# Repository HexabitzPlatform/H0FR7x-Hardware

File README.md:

# H0FR7x-Hardware
Hexabitz SPST 18V/20A MOSFET Switch Module Hardware Design

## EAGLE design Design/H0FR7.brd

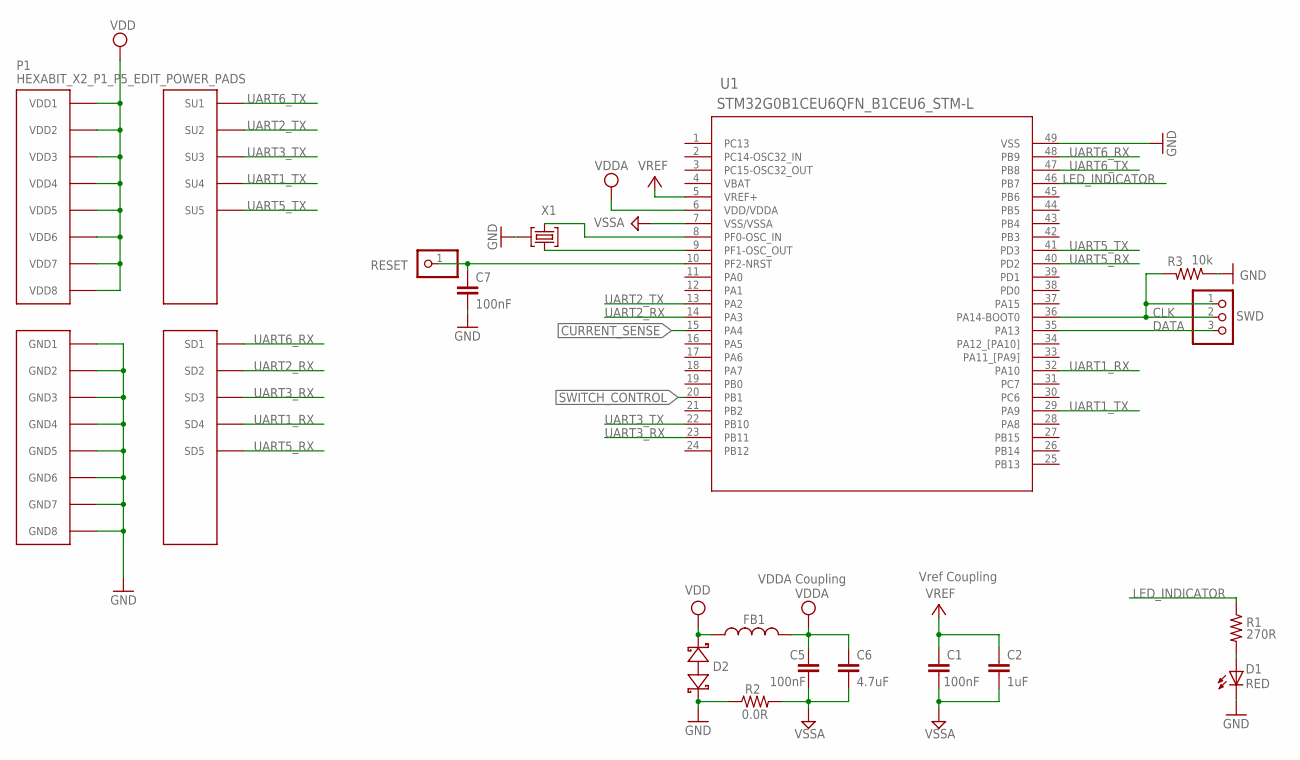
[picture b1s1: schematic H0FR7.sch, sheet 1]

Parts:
C1, C7: 100nF; C-0603; TOLERANCE 10%; VOLTAGE_RATING 10V; MPN C0603C104K8RACTU
C2: 1uF; C-0805
C5: 100nF; C-0603
C6: 4.7uF; C-0805
D1: RED; VLMS1300-GS08; MPN VLMS1300-GS08
D2: BOURNS_CDSOD323-T03SCBOURNS_CDSOD323-T03SC_0_0; BOURNS_CDSOD323-T03SC_0
FB1: FB-0603
P1: HEXABIT_X2_P1_P5_EDIT_POWER_PADS
R1: 270R; R-0603
R2: 0.0R; R-0603
R3: 10k; R-0603; TOLERANCE 5%; MPN RC0603JR-0710KL
RESET: R; 1X01
SWD: PINHD-1X3SWD; SWD
TRIMBLE-LOGO2: HEXA-LOGO
U1: STM32G0B1CEU6QFN_B1CEU6_STM-L; QFN_B1CEU6_STM-L
X1: XTALL_CSTCE8M00G52

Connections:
CLK: R3.2, SWD.1, SWD.2, U1.36 (PA14-BOOT0)
CURRENT_SENSE: U1.15 (PA4); also elsewhere on the board
DATA: SWD.3, U1.35 (PA13)
GND: C7.2, D1.C, D2.2 (C), P1.PAD_PD11 (GND1), P1.PAD_PD12 (GND2), P1.PAD_PD13 (GND3), P1.PAD_PD14 (GND4), P1.PAD_PD17 (GND5), P1.PAD_PD18 (GND6), P1.PAD_PD19 (GND7), P1.PAD_PD20 (GND8), R2.1, R3.1, U1.49 (VSS), X1.P$2 (2)
LED_INDICATOR: R1.1, U1.46 (PB7)
unnamed: U1.9 (PF1-OSC_OUT), X1.P$3 (3)
unnamed: U1.8 (PF0-OSC_IN), X1.P$1 (1)
unnamed: D1.A, R1.2
unnamed: C7.1, RESET.1, U1.10 (PF2-NRST)
SWITCH_CONTROL: U1.20 (PB1); also elsewhere on the board
UART1_RX: P1.PAD_PD4 (SD4), U1.32 (PA10)
UART1_TX: P1.PAD_PU4 (SU4), U1.29 (PA9)
UART2_RX: P1.PAD_PD2 (SD2), U1.14 (PA3)
UART2_TX: P1.PAD_PU2 (SU2), U1.13 (PA2)
UART3_RX: P1.PAD_PD3 (SD3), U1.23 (PB11)
UART3_TX: P1.PAD_PU3 (SU3), U1.22 (PB10)
UART5_RX: P1.PAD_PD5 (SD5), U1.40 (PD2)
UART5_TX: P1.PAD_PU5 (SU5), U1.41 (PD3)
UART6_RX: P1.PAD_PD1 (SD1), U1.48 (PB9)
UART6_TX: P1.PAD_PU1 (SU1), U1.47 (PB8)
VDD: D2.1 (A), FB1.1, P1.PAD_PU11 (VDD1), P1.PAD_PU12 (VDD2), P1.PAD_PU13 (VDD3), P1.PAD_PU14 (VDD4), P1.PAD_PU17 (VDD5), P1.PAD_PU18 (VDD6), P1.PAD_PU19 (VDD7), P1.PAD_PU20 (VDD8)
VDDA: C5.1, C6.1, FB1.2, U1.6 (VDD/VDDA); also elsewhere on the board
VREF: C1.1, C2.1, U1.5 (VREF+)
VSSA: C1.2, C2.2, C5.2, C6.2, R2.2, U1.7 (VSS/VSSA); also elsewhere on the board

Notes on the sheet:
Vref Coupling
VDDA Coupling

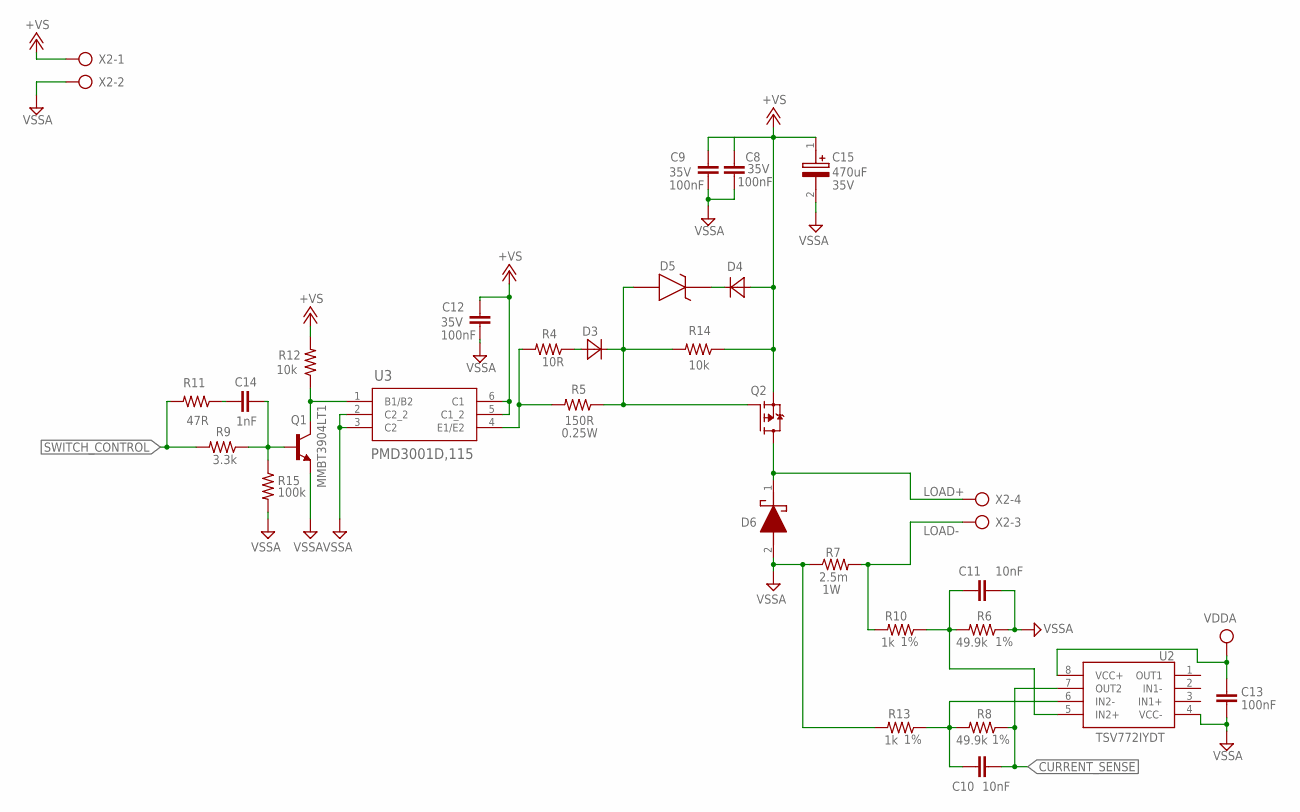
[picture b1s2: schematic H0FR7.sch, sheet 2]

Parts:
C8, C9, C12: C-0603; VOLTAGE_RATING 35V
C10, C11: 10nF; C-0603; TOLERANCE 10V; VOLTAGE_RATING 10%; MPN C0603C104K8RACTU
C13: 100nF; C-0603; TOLERANCE 10V; VOLTAGE_RATING 10%; MPN C0603C104K8RACTU
C14: 1nF; C-0603; TOLERANCE 10%; VOLTAGE_RATING 10V; MPN C0603C104K8RACTU
C15: ESH477M035AH3AA; CAPPRD500W60D1000H1700
D3, D4: DIOD-SOD-123; SOD123; MPN 1N4148W-7-F
D5: MMSZ4705T1GMMSZ4705T1G; DIO_MMSZ4700T1G; VOLTAGE 18V; MPN MMSZ4678T1G
D6: V8PAM10S-M3_H; V8PAM10SHM3H
Q1: MMBT3904LT1
Q2: STD36P4LLF6; DPAK-3
R4: 10R; R-0603; TOLERANCE 5%; MPN RC0603JR-07680KL
R5: 150R; R-0603; MPN CRGP0603F150R
R6, R8: 49.9k; R-0603; TOLERANCE 1%; MPN RC0603JR-071KL
R7: 2.5m; R1206; MPN PA1206FRE472U5Z
R9: 3.3k; R-0603; TOLERANCE 5%; MPN RC0603JR-07680KL
R10, R13: 1k; R-0603; TOLERANCE 1%; MPN RC0603JR-071KL
R11: 47R; R-0603; TOLERANCE 5%; MPN RC0603JR-07680KL
R12: 10k; R-0603; TOLERANCE 5%; MPN RC0603JR-0710KL
R14: 10k; R-0603; TOLERANCE 5%; MPN RC0603JR-07680KL
R15: 100k; R-0603; TOLERANCE 5%; MPN RC0603JR-07680KL
U2: TSV772IYDT; SOIC127P600X175-8N
U3: PMD3001D,115; SOT457_NEX
X2: AK300/4

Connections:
+VS: C8.2, C9.2, C12.2, C15.1 (+), D4.1 (A), Q2.3 (S), R12.2, R14.1, U3.5 (C1_2), U3.6 (C1), X2.1
CURRENT_SENSE: C10.2, R8.1, U2.7 (OUT2); also elsewhere on the board
LOAD+: D6.1 (K), Q2.4 (D), X2.4
LOAD-: R7.2, R10.2, X2.3
unnamed: Q1.3 (C), R12.1, U3.1 (B1/B2)
unnamed: C11.1, R6.2, R10.1, U2.5 (IN2+)
unnamed: D4.2 (C), D5.K
unnamed: C10.1, R8.2, R13.1, U2.6 (IN2-)
unnamed: D3.1 (A), R4.1
unnamed: C14.2, Q1.1 (B), R9.1, R15.1
unnamed: C14.1, R11.1
unnamed: R4.2, R5.2, U3.4 (E1/E2)
unnamed: D3.2 (C), D5.A, Q2.1 (G), R5.1, R14.2
SWITCH_CONTROL: R9.2, R11.2; also elsewhere on the board
VDDA: C13.2, U2.8 (VCC+); also elsewhere on the board
VSSA: C8.1, C9.1, C11.2, C12.1, C13.1, C15.2 (-), D6.2 (A), Q1.2 (E), R6.1, R7.1, R13.2, R15.2, U2.4 (VCC-), U3.2 (C2_2), U3.3 (C2), X2.2; also elsewhere on the board

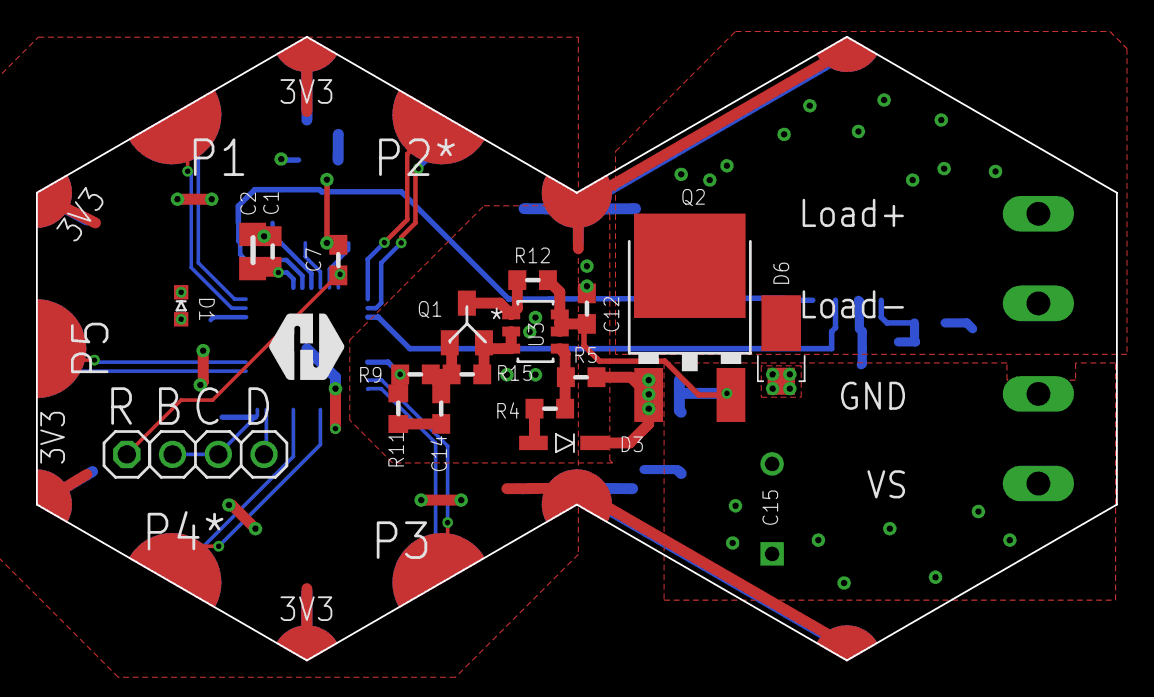
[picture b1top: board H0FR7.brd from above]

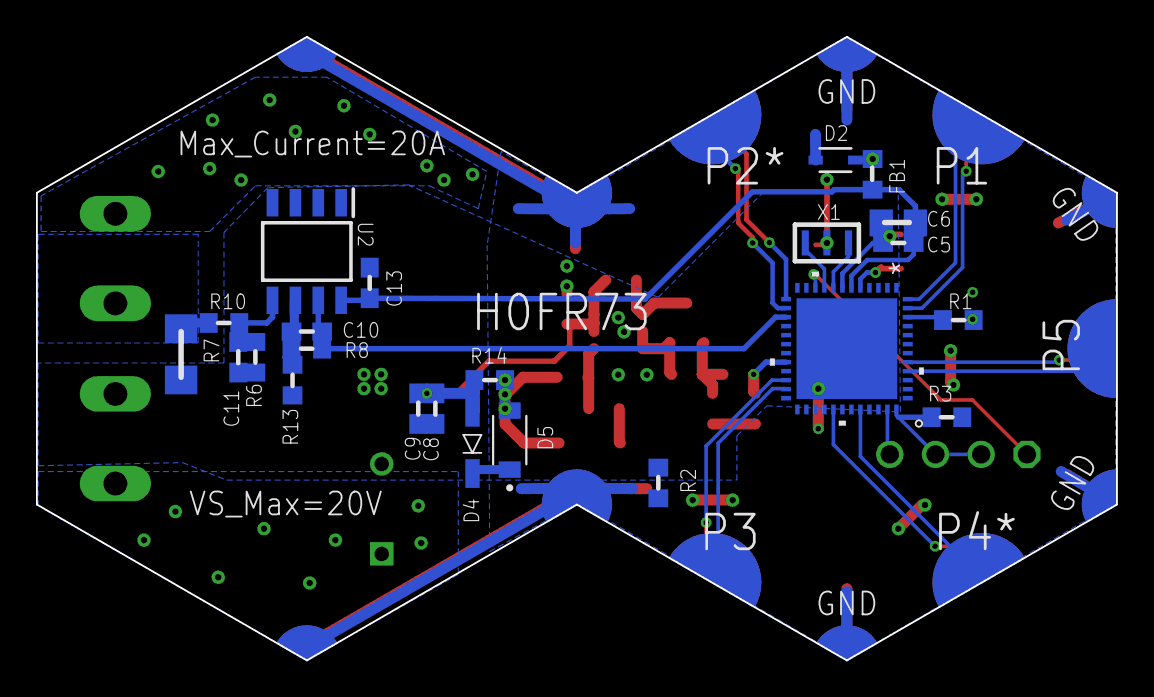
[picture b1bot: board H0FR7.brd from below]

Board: 2 copper layers, 60.0 x 34.6 mm, 46 parts (23 on the bottom side), 36 nets.

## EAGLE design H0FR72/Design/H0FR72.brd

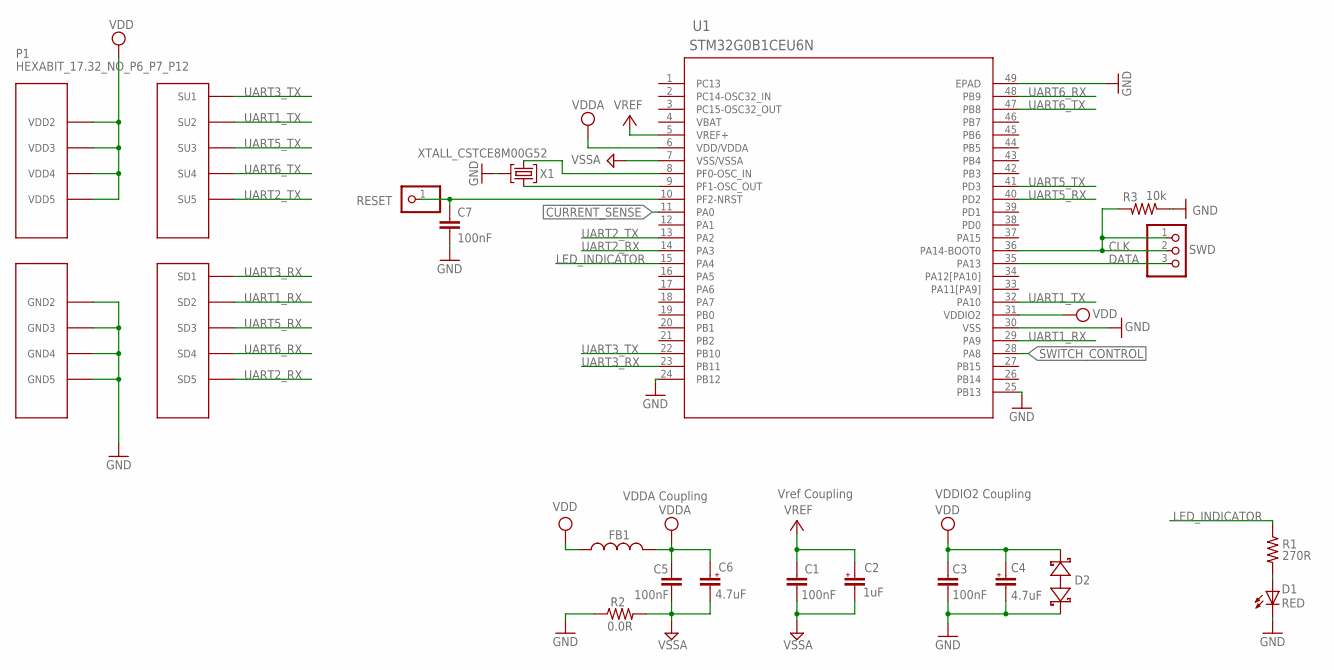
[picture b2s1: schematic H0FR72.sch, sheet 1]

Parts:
C1, C3, C7: 100nF; C-0402; TOLERANCE 10%; VOLTAGE_RATING 10V; MPN C0603C104K8RACTU
C2: 1uF; C-0603-POL; TOLERANCE 10%; VOLTAGE_RATING 16V; MPN CC0805KKX7R7BB105
C4, C6: 4.7uF; C-0603-POL; TOLERANCE 10%; VOLTAGE_RATING 25V; MPN GRM21BC81E475KA12L
C5: 100nF; C-0603
D1: RED; VLMS1300-GS08; MPN VLMS1300-GS08
D2: BOURNS_CDSOD323-T03SCBOURNS_CDSOD323-T03SC_0_0; BOURNS_CDSOD323-T03SC_0
FB1: FB-0603
P1: HEXABIT_17.32_NO_P6_P7_P12
R1: 270R; R-0603
R2: 0.0R; R-0603
R3: 10k; R-0402; TOLERANCE 5%; MPN RC0603JR-0710KL
RESET: R; 1X01
SWD: PINHD-1X3SWD; SWD
TRIMBLE-LOGO2: HEXA-LOGO
U1: STM32G0B1CEU6N; HEXABITZ_ICS_QFN_B1CEU6_STM-L
X1: XTALL_CSTCE8M00G52

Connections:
CLK: R3.2, SWD.1, SWD.2, U1.36 (PA14-BOOT0)
CURRENT_SENSE: U1.11 (PA0); also elsewhere on the board
DATA: SWD.3, U1.35 (PA13)
GND: C3.2, C4.2, C7.2, D1.C, D2.2 (C), P1.PAD_PD8 (GND2), P1.PAD_PD9 (GND3), P1.PAD_PD10 (GND4), P1.PAD_PD11 (GND5), R2.1, R3.1, U1.24 (PB12), U1.25 (PB13), U1.30 (VSS), U1.49 (EPAD), X1.P$2 (2)
LED_INDICATOR: R1.1, U1.15 (PA4)
unnamed: U1.9 (PF1-OSC_OUT), X1.P$3 (3)
unnamed: U1.8 (PF0-OSC_IN), X1.P$1 (1)
unnamed: D1.A, R1.2
unnamed: C7.1, RESET.1, U1.10 (PF2-NRST)
SWITCH_CONTROL: U1.28 (PA8); also elsewhere on the board
UART1_RX: P1.PAD_PD2 (SD2), U1.29 (PA9)
UART1_TX: P1.PAD_PU2 (SU2), U1.32 (PA10)
UART2_RX: P1.PAD_PD5 (SD5), U1.14 (PA3)
UART2_TX: P1.PAD_PU5 (SU5), U1.13 (PA2)
UART3_RX: P1.PAD_PD1 (SD1), U1.23 (PB11)
UART3_TX: P1.PAD_PU1 (SU1), U1.22 (PB10)
UART5_RX: P1.PAD_PD3 (SD3), U1.40 (PD2)
UART5_TX: P1.PAD_PU3 (SU3), U1.41 (PD3)
UART6_RX: P1.PAD_PD4 (SD4), U1.48 (PB9)
UART6_TX: P1.PAD_PU4 (SU4), U1.47 (PB8)
VBAT: U1.4 (VBAT)
VDD: C3.1, C4.1, D2.1 (A), FB1.1, P1.PAD_PU8 (VDD2), P1.PAD_PU9 (VDD3), P1.PAD_PU10 (VDD4), P1.PAD_PU11 (VDD5), U1.31 (VDDIO2)
VDDA: C5.1, C6.1, FB1.2, U1.6 (VDD/VDDA)
VREF: C1.1, C2.1, U1.5 (VREF+)
VSSA: C1.2, C2.2, C5.2, C6.2, R2.2, U1.7 (VSS/VSSA); also elsewhere on the board

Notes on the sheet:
VDDIO2 Coupling
Vref Coupling
VDDA Coupling

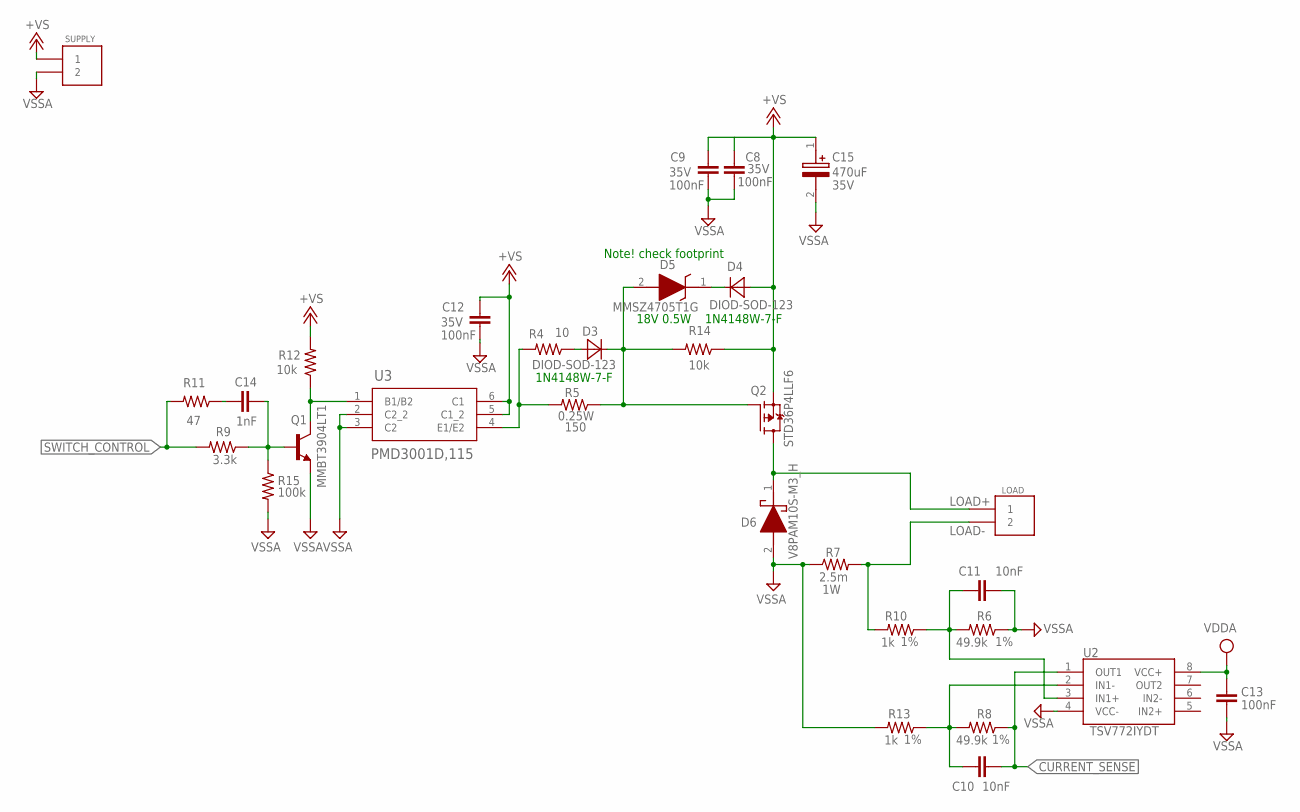
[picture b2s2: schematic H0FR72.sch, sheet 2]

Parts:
C8, C9, C12: C-0402; VOLTAGE_RATING 35V
C10, C11: 10nF; C-0402; TOLERANCE 10V; VOLTAGE_RATING 10%; MPN C0603C104K8RACTU
C13: 100nF; C-0402; TOLERANCE 10V; VOLTAGE_RATING 10%; MPN C0603C104K8RACTU
C14: 1nF; C-0402; TOLERANCE 10%; VOLTAGE_RATING 10V; MPN C0603C104K8RACTU
C15: ESH477M035AH3AA; CAPPRD500W60D1000H1700
D3, D4: DIOD-SOD-123; SOD123
D5: MMSZ4705T1G; SOD3716X135N
D6: V8PAM10S-M3_H; V8PAM10SHM3H
LOAD: 1546111-2
Q1: MMBT3904LT1
Q2: STD36P4LLF6; DPAK-3
R4: 10; R-0402; TOLERANCE 5%; MPN RC0603JR-07680KL
R5: 150; R-0402; TOLERANCE 5%; MPN RC0603JR-07680KL
R6, R8: 49.9k; R-0402; TOLERANCE 1%; MPN RC0603JR-071KL
R7: 2.5m; R2512
R9: 3.3k; R-0402; TOLERANCE 5%; MPN RC0603JR-07680KL
R10, R13: 1k; R-0402; TOLERANCE 1%; MPN RC0603JR-071KL
R11: 47; R-0402; TOLERANCE 5%; MPN RC0603JR-07680KL
R12: 10k; R-0402; TOLERANCE 5%; MPN RC0603JR-0710KL
R14: 10k; R-0402; TOLERANCE 5%; MPN RC0603JR-07680KL
R15: 100k; R-0402; TOLERANCE 5%; MPN RC0603JR-07680KL
SUPPLY: 1546111-2
TRIMBLE-LOGO1: HEXA-LOGO
U2: TSV772IYDT; SOIC127P600X175-8N
U3: PMD3001D,115; SOT457_NEX

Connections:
+VS: C8.2, C9.2, C12.2, C15.1 (+), D4.1 (A), Q2.3 (S), R12.2, R14.1, SUPPLY.1, U3.5 (C1_2), U3.6 (C1)
CURRENT_SENSE: C10.2, R8.1, U2.1 (OUT1); also elsewhere on the board
LOAD+: D6.1 (K), LOAD.1, Q2.4 (D)
LOAD-: LOAD.2, R7.2, R10.2
unnamed: Q1.3 (C), R12.1, U3.1 (B1/B2)
unnamed: C11.1, R6.2, R10.1, U2.3 (IN1+)
unnamed: D4.2 (C), D5.1 (K)
unnamed: C10.1, R8.2, R13.1, U2.2 (IN1-)
unnamed: D3.1 (A), R4.1
unnamed: C14.2, Q1.1 (B), R9.1, R15.1
unnamed: C14.1, R11.1
unnamed: R4.2, R5.2, U3.4 (E1/E2)
unnamed: D3.2 (C), D5.2 (A), Q2.1 (G), R5.1, R14.2
SWITCH_CONTROL: R9.2, R11.2; also elsewhere on the board
VCC: C13.2, U2.8 (VCC+)
VSSA: C8.1, C9.1, C11.2, C12.1, C13.1, C15.2 (-), D6.2 (A), Q1.2 (E), R6.1, R7.1, R13.2, R15.2, SUPPLY.2, U2.4 (VCC-), U3.2 (C2_2), U3.3 (C2); also elsewhere on the board

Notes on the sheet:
1N4148W-7-F
18V 0.5W
Note! check footprint

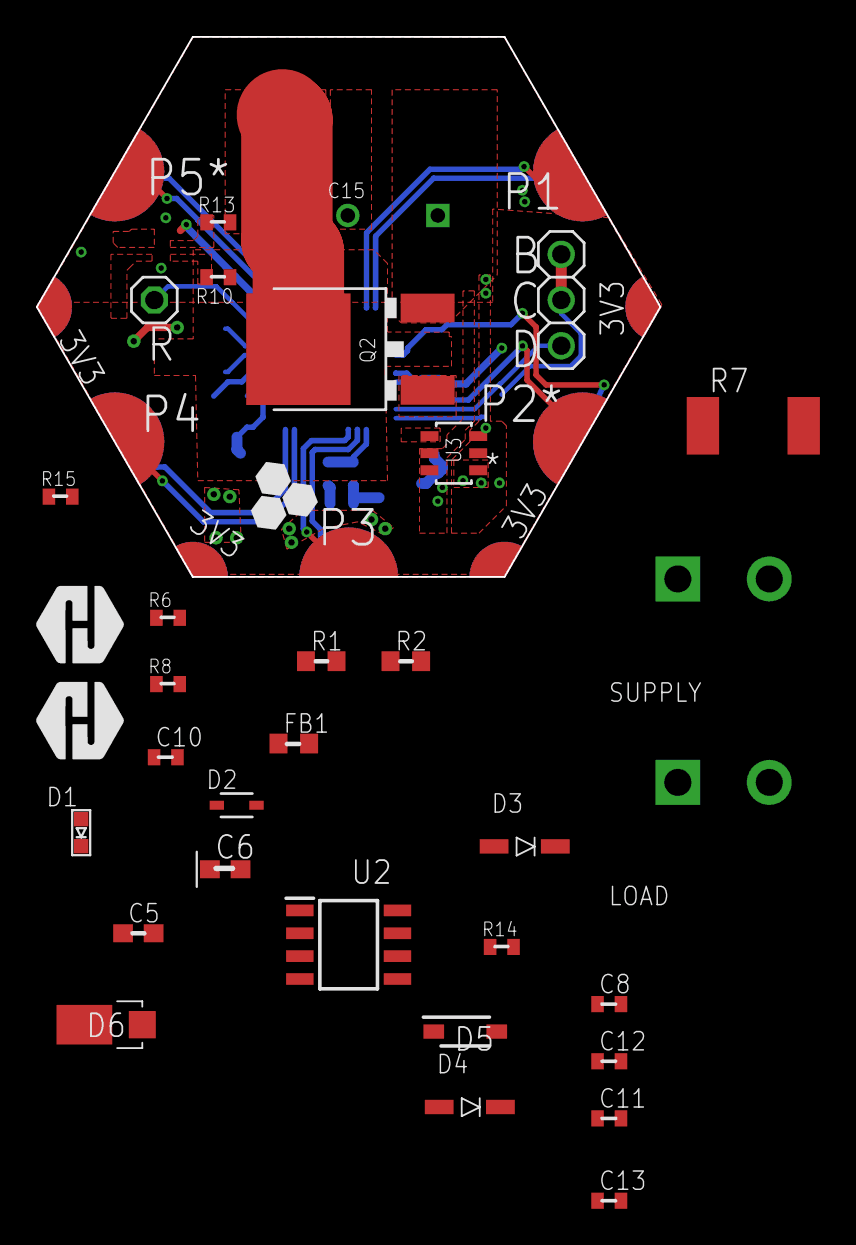
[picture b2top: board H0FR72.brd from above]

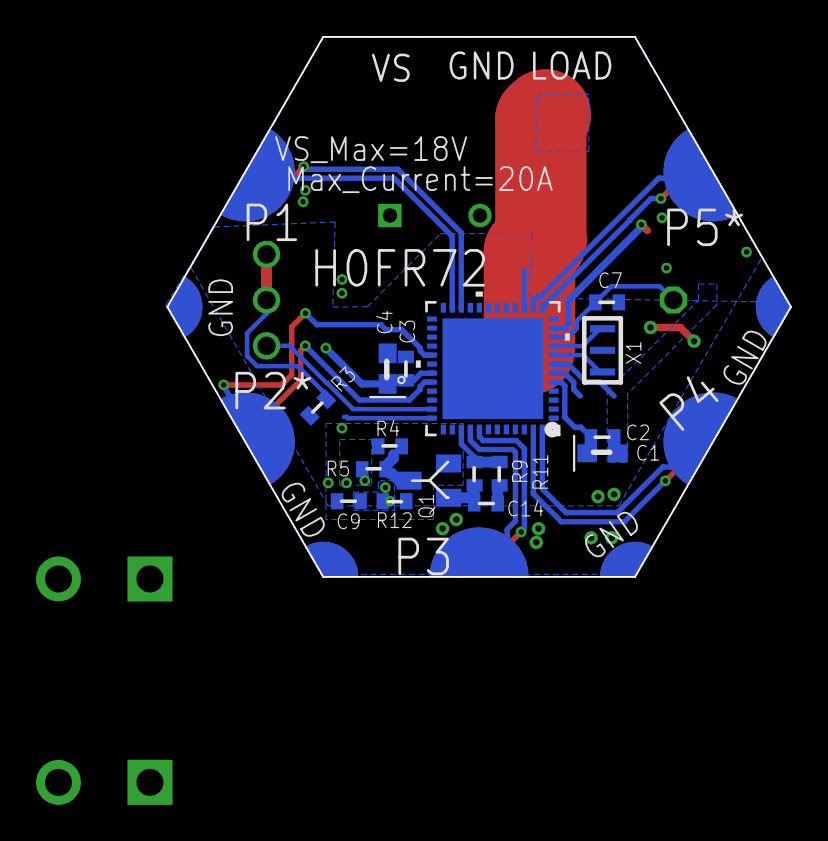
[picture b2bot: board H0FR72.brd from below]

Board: 2 copper layers, 34.6 x 30.0 mm, 50 parts (17 on the bottom side), 37 nets.

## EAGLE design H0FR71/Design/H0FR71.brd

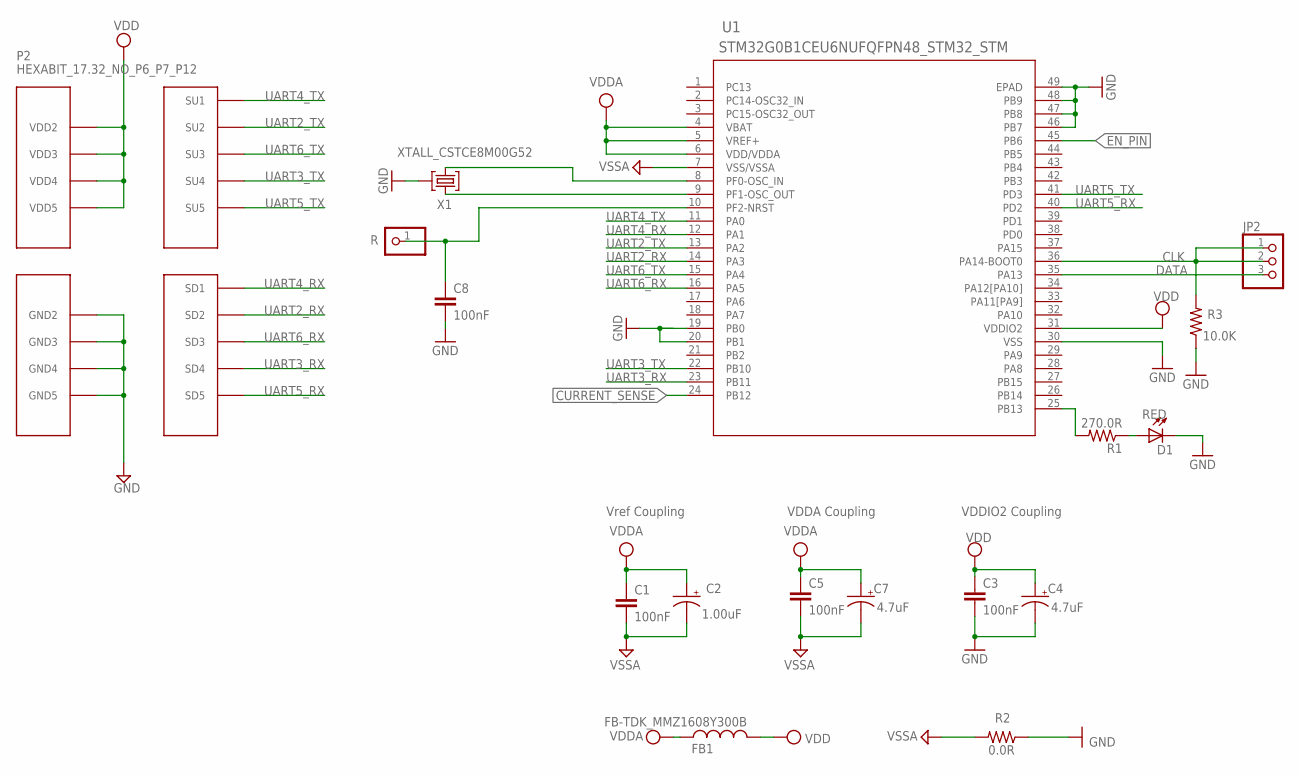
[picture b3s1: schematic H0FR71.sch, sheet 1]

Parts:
C1, C3, C8: 100nF; C-0603; TOLERANCE 10%; VOLTAGE_RATING 10V; MPN C0603C104K8RACTU
C2: 1.00uF; C-0805-POL; TOLERANCE 10%; VOLTAGE_RATING 16V; MPN CC0805KKX7R7BB105
C4, C7: 4.7uF; C-0805-POL; TOLERANCE 10%; VOLTAGE_RATING 25V; MPN GRM21BC81E475KA12L
C5: 100nF; C-0603; TOLERANCE 10%; VOLTAGE_RATING 10; MPN C0603C104K8RACTU
D1: RED; VLMS1300-GS08; MPN VLMS1300-GS08
FB1: FB-TDK_MMZ1608Y300B; MPN MMZ1608Y300B
JP2: PINHD-1X3; 1X03
P2: HEXABIT_17.32_NO_P6_P7_P12
R: PINHD-1X1; 1X01
R1: 270.0R; R-0603; TOLERANCE 1%; MPN RC0603FR-07270RL
R2: 0.0R; R-0603; MPN RC0603JR-070RL
R3: 10.0K; R-0603; TOLERANCE 5%; MPN RC0603JR-0710KL
U1: STM32G0B1CEU6NUFQFPN48_STM32_STM; UFQFPN48_STM32_STM
X1: XTALL_CSTCE8M00G52

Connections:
AGND: C1.2, C2.2 (-), C5.2, C7.2 (-), R2.2, U1.7 (VSS/VSSA); also elsewhere on the board
CLK: JP2.1, JP2.2, R3.2, U1.36 (PA14-BOOT0)
CURRENT_SENSE: U1.24 (PB12); also elsewhere on the board
DATA: JP2.3, U1.35 (PA13)
EN_PIN: U1.45 (PB6); also elsewhere on the board
GND: C3.2, C4.2 (-), C8.2, D1.C, P2.PAD_PD8 (GND2), P2.PAD_PD9 (GND3), P2.PAD_PD10 (GND4), P2.PAD_PD11 (GND5), R2.1, R3.1, U1.19 (PB0), U1.20 (PB1), U1.30 (VSS), U1.46 (PB7), U1.47 (PB8), U1.48 (PB9), U1.49 (EPAD), X1.P$2 (2); also elsewhere on the board
unnamed: U1.9 (PF1-OSC_OUT), X1.P$3 (3)
unnamed: U1.8 (PF0-OSC_IN), X1.P$1 (1)
unnamed: R1.2, U1.25 (PB13)
unnamed: D1.A, R1.1
unnamed: C8.1, R.1, U1.10 (PF2-NRST)
UART2_RX: P2.PAD_PD2 (SD2), U1.14 (PA3)
UART2_TX: P2.PAD_PU2 (SU2), U1.13 (PA2)
UART3_RX: P2.PAD_PD4 (SD4), U1.23 (PB11)
UART3_TX: P2.PAD_PU4 (SU4), U1.22 (PB10)
UART4_RX: P2.PAD_PD1 (SD1), U1.12 (PA1)
UART4_TX: P2.PAD_PU1 (SU1), U1.11 (PA0)
UART5_RX: P2.PAD_PD5 (SD5), U1.40 (PD2)
UART5_TX: P2.PAD_PU5 (SU5), U1.41 (PD3)
UART6_RX: P2.PAD_PD3 (SD3), U1.16 (PA5)
UART6_TX: P2.PAD_PU3 (SU3), U1.15 (PA4)
VDD: C3.1, C4.1 (+), FB1.2, P2.PAD_PU8 (VDD2), P2.PAD_PU9 (VDD3), P2.PAD_PU10 (VDD4), P2.PAD_PU11 (VDD5), U1.31 (VDDIO2)
VDDA: C1.1, C2.1 (+), C5.1, C7.1 (+), FB1.1, U1.4 (VBAT), U1.5 (VREF+), U1.6 (VDD/VDDA); also elsewhere on the board

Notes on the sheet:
VDDA Coupling
VDDIO2 Coupling
Vref Coupling

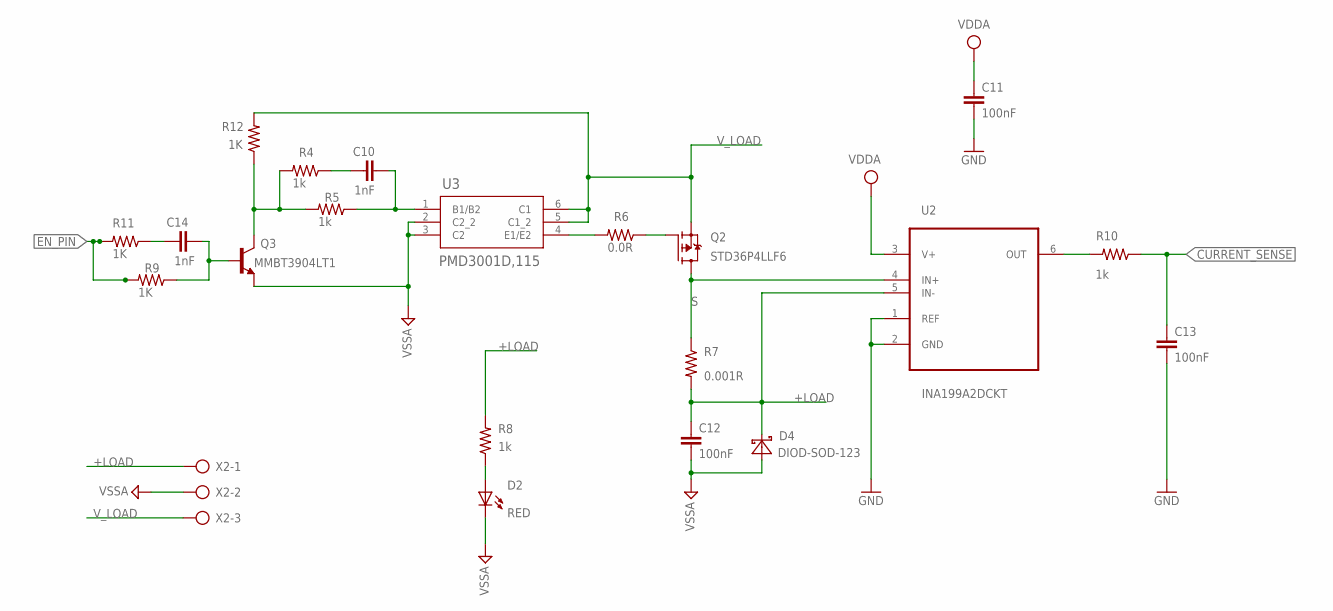
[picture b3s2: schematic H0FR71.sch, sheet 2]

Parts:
C10, C14: 1nF; C-0603; TOLERANCE 10%; VOLTAGE_RATING 10V; MPN C0603C104K8RACTU
C11: 100nF; C-0603; TOLERANCE 10V; VOLTAGE_RATING 10%; MPN C0603C104K8RACTU
C12, C13: 100nF; C-0603; TOLERANCE 10%; VOLTAGE_RATING 10V; MPN C0603C104K8RACTU
D2: RED; VLMS1300-GS08; MPN VLMO1300-GS08
D4: DIOD-SOD-123; SOD123
Q2: STD36P4LLF6; DPAK-3
Q3: MMBT3904LT1
R4, R5: 1k; R-0603; TOLERANCE 5%; MPN RC0603JR-07680KL
R6: 0.0R; R-0603; MPN RC0603JR-070RL
R7: 0.001R; R2512
R8: 1k; R-0603; TOLERANCE 1%; MPN RC0603JR-071KL
R9, R11: 1K; R-0603; TOLERANCE 5%; MPN RC0603JR-07680KL
R10: 1k; R-0603; TOLERANCE 5%; MPN RC0603JR-071KL
R12: 1K; R-0603; TOLERANCE 5%; MPN RC0603JR-0710KL
U2: INA199A2DCKT; SOT65P210X110-6N
U3: PMD3001D,115; SOT457_NEX
X2: AK500/3

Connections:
+LOAD: C12.1, D4.2 (C), R7.2, R8.2, U2.5 (IN-), X2.1
AGND: C12.2, D2.C, D4.1 (A), Q3.2 (E), U3.2 (C2_2), U3.3 (C2), X2.2; also elsewhere on the board
CURRENT_SENSE: C13.1, R10.1; also elsewhere on the board
EN_PIN: R9.2, R11.2; also elsewhere on the board
GND: C11.2, C13.2, U2.1 (REF), U2.2 (GND); also elsewhere on the board
unnamed: C10.2, R5.1, U3.1 (B1/B2)
unnamed: D2.A, R8.1
unnamed: R10.2, U2.6 (OUT)
unnamed: Q2.1 (G), R6.1
unnamed: Q3.3 (C), R4.2, R5.2, R12.1
unnamed: R6.2, U3.4 (E1/E2)
unnamed: C10.1, R4.1
unnamed: C14.2, Q3.1 (B), R9.1
unnamed: C14.1, R11.1
S: Q2.4 (D), R7.1, U2.4 (IN+)
VDDA: C11.1, U2.3 (V+); also elsewhere on the board
V_LOAD: Q2.3 (S), R12.2, U3.5 (C1_2), U3.6 (C1), X2.3

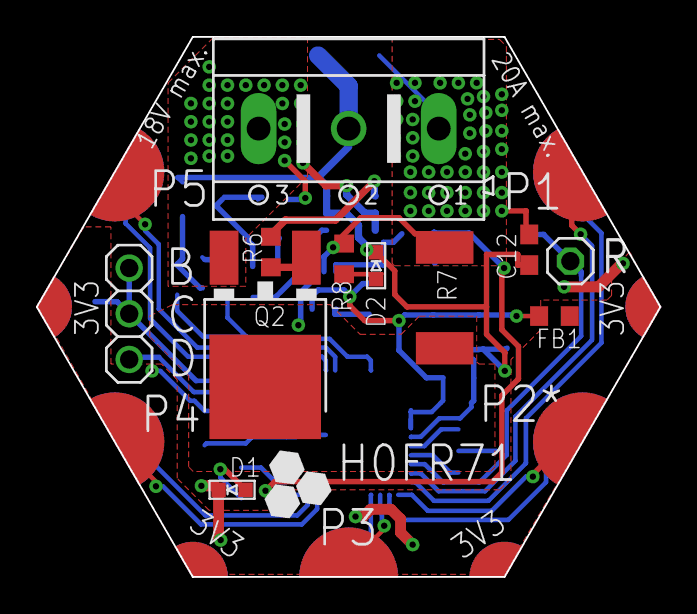
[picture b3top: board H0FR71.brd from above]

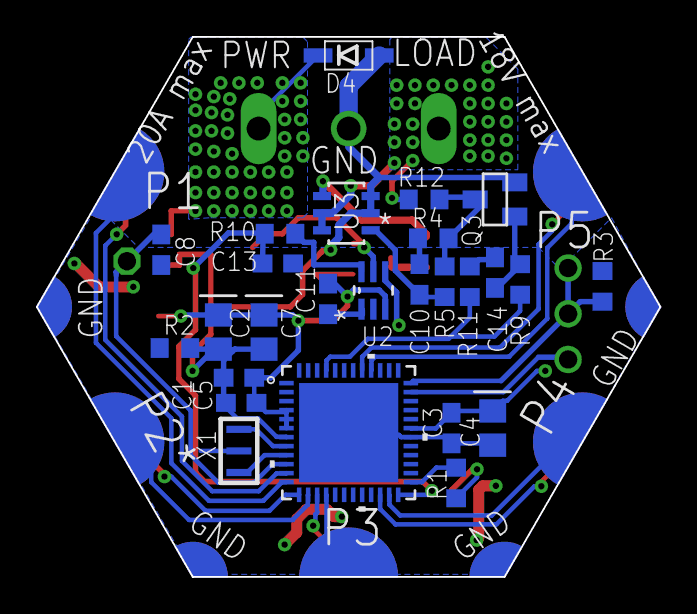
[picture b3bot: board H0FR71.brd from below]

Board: 2 copper layers, 34.6 x 30.0 mm, 38 parts (26 on the bottom side), 35 nets.

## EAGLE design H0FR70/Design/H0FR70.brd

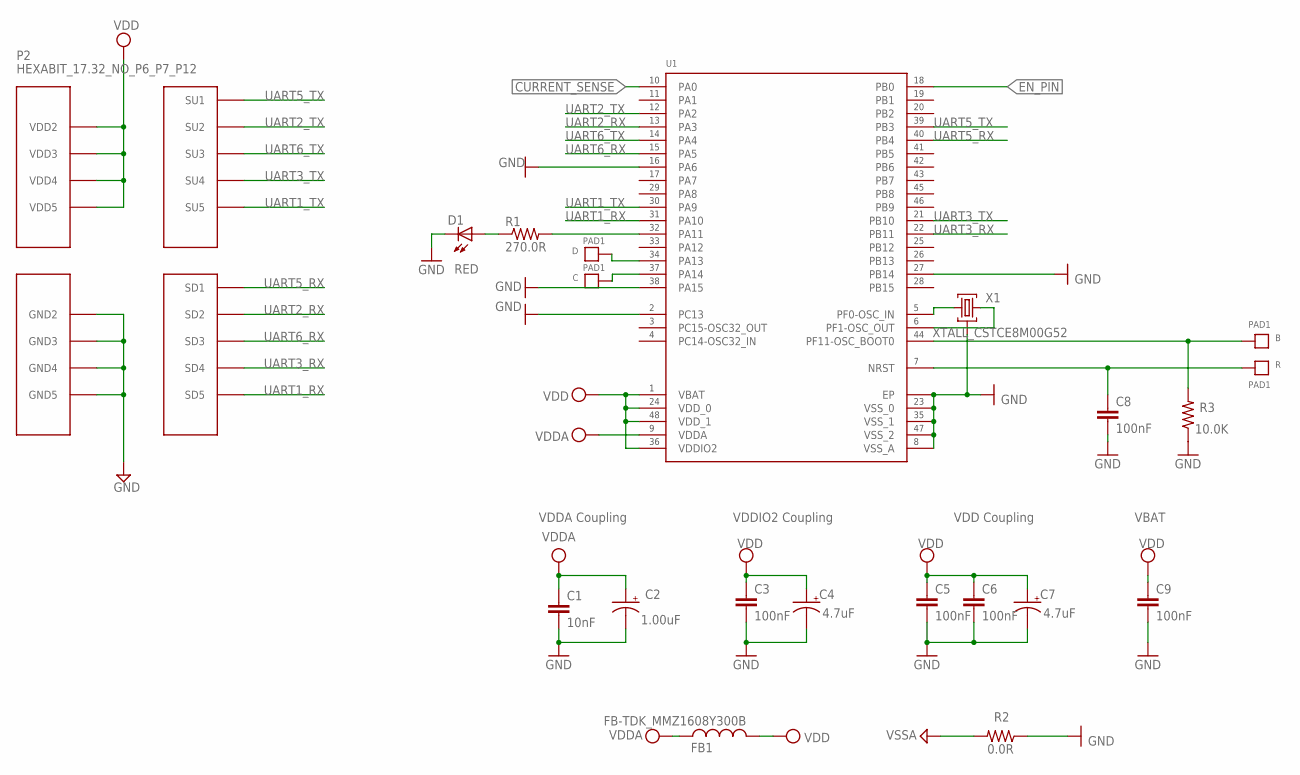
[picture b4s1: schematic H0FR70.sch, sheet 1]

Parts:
B: PAD1
C: PAD1
C1: 10nF; C-0603; TOLERANCE 10%; VOLTAGE_RATING 50V; MPN C0603C103K5RACTU
C2: 1.00uF; C-0805-POL; TOLERANCE 10%; VOLTAGE_RATING 16V; MPN CC0805KKX7R7BB105
C3, C6, C8: 100nF; C-0603; TOLERANCE 10%; VOLTAGE_RATING 10V; MPN C0603C104K8RACTU
C4, C7: 4.7uF; C-0805-POL; TOLERANCE 10%; VOLTAGE_RATING 25V; MPN GRM21BC81E475KA12L
C5: 100nF; C-0603; TOLERANCE 10%; VOLTAGE_RATING 10; MPN C0603C104K8RACTU
C9: 100nF; C-0603; TOLERANCE 10V; VOLTAGE_RATING 10%; MPN C0603C104K8RACTU
D: PAD1
D1: RED; VLMS1300-GS08; MPN VLMS1300-GS08
FB1: FB-TDK_MMZ1608Y300B; MPN MMZ1608Y300B
P2: HEXABIT_17.32_NO_P6_P7_P12
R: PAD1
R1: 270.0R; R-0603; TOLERANCE 1%; MPN RC0603FR-07270RL
R2: 0.0R; R-0603; MPN RC0603JR-070RL
R3: 10.0K; R-0603; TOLERANCE 5%; MPN RC0603JR-0710KL
U1: STM32F091CBU6
X1: XTALL_CSTCE8M00G52

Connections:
AGND: R2.2; also elsewhere on the board
B1: B.P$1, B.P$2, R3.2, U1.P$44 (PF11-OSC_BOOT0)
CURRENT_SENSE: U1.P$10 (PA0); also elsewhere on the board
EN_PIN: U1.P$18 (PB0); also elsewhere on the board
GND: C1.2, C2.2 (-), C3.2, C4.2 (-), C5.2, C6.2, C7.2 (-), C8.2, C9.2, D1.C, P2.PAD_PD8 (GND2), P2.PAD_PD9 (GND3), P2.PAD_PD10 (GND4), P2.PAD_PD11 (GND5), R2.1, R3.1, U1.EP, U1.P$2 (PC13), U1.P$8 (VSS_A), U1.P$16 (PA6), U1.P$23 (VSS_0), U1.P$27 (PB14), U1.P$35 (VSS_1), U1.P$38 (PA15), U1.P$47 (VSS_2), X1.P$2 (2); also elsewhere on the board
unnamed: D.P$1, D.P$2, U1.P$34 (PA13)
unnamed: C.P$1, C.P$2, U1.P$37 (PA14)
unnamed: R1.2, U1.P$32 (PA11)
unnamed: D1.A, R1.1
unnamed: U1.P$5 (PF0-OSC_IN), X1.P$1 (1)
unnamed: U1.P$6 (PF1-OSC_OUT), X1.P$3 (3)
R1: C8.1, R.P$1, R.P$2, U1.P$7 (NRST)
UART1_RX: P2.PAD_PD5 (SD5), U1.P$31 (PA10)
UART1_TX: P2.PAD_PU5 (SU5), U1.P$30 (PA9)
UART2_RX: P2.PAD_PD2 (SD2), U1.P$13 (PA3)
UART2_TX: P2.PAD_PU2 (SU2), U1.P$12 (PA2)
UART3_RX: P2.PAD_PD4 (SD4), U1.P$22 (PB11)
UART3_TX: P2.PAD_PU4 (SU4), U1.P$21 (PB10)
UART5_RX: P2.PAD_PD1 (SD1), U1.P$40 (PB4)
UART5_TX: P2.PAD_PU1 (SU1), U1.P$39 (PB3)
UART6_RX: P2.PAD_PD3 (SD3), U1.P$15 (PA5)
UART6_TX: P2.PAD_PU3 (SU3), U1.P$14 (PA4)
VDD: C3.1, C4.1 (+), C5.1, C6.1, C7.1 (+), C9.1, FB1.2, P2.PAD_PU8 (VDD2), P2.PAD_PU9 (VDD3), P2.PAD_PU10 (VDD4), P2.PAD_PU11 (VDD5), U1.P$1 (VBAT), U1.P$24 (VDD_0), U1.P$36 (VDDIO2), U1.P$48 (VDD_1)
VDDA: C1.1, C2.1 (+), FB1.1, U1.P$9 (VDDA); also elsewhere on the board

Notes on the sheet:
VDDA Coupling
VDDIO2 Coupling
VDD Coupling
VBAT

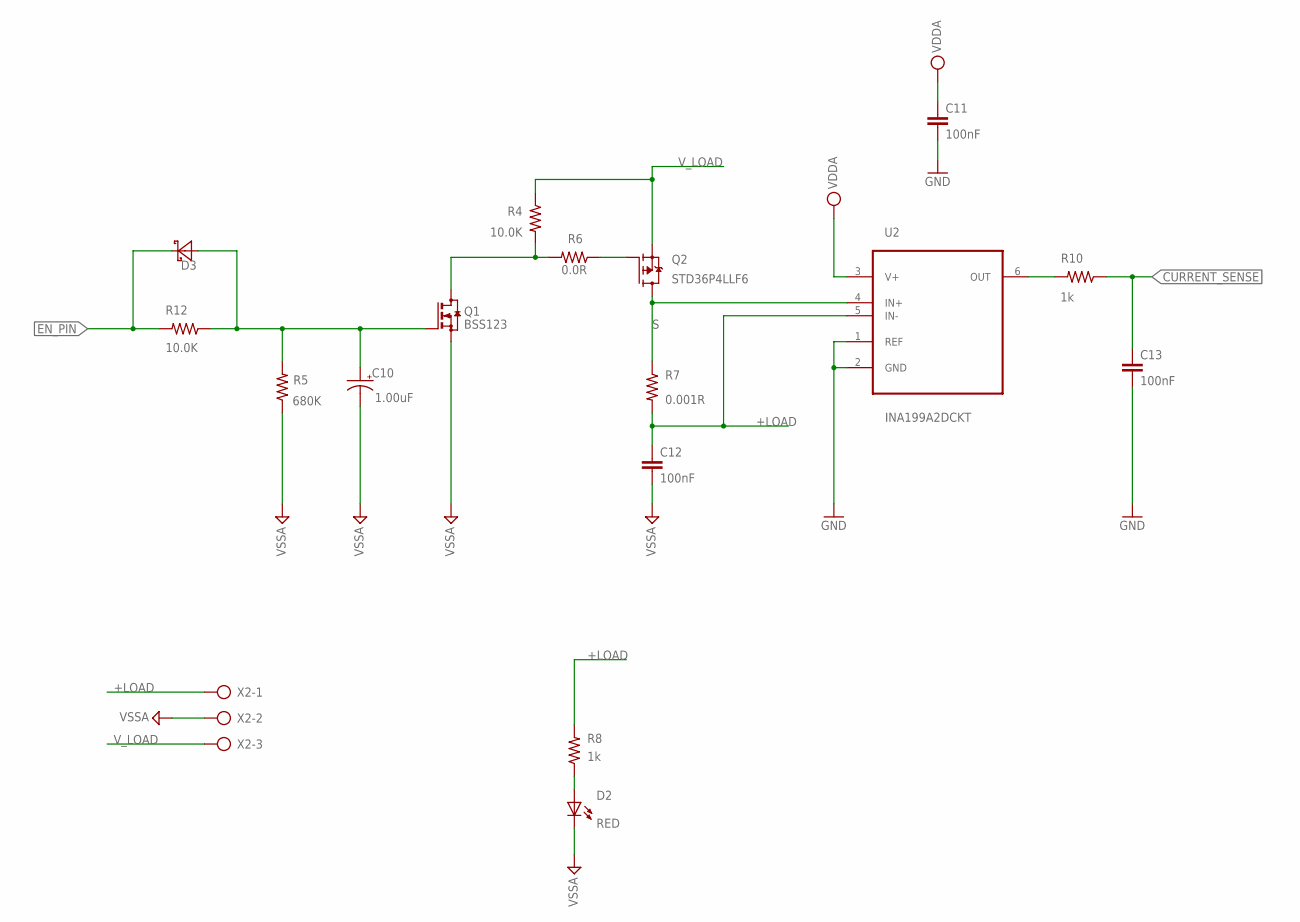
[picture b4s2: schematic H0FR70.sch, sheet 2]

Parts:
C10: 1.00uF; C-0805-POL; TOLERANCE 10%; VOLTAGE_RATING 16V; MPN CC0805KKX7R7BB105
C11: 100nF; C-0603; TOLERANCE 10V; VOLTAGE_RATING 10%; MPN C0603C104K8RACTU
C12, C13: 100nF; C-0603; TOLERANCE 10%; VOLTAGE_RATING 10V; MPN C0603C104K8RACTU
D2: RED; VLMS1300-GS08; MPN VLMO1300-GS08
D3: SMD-DIODE-SCHOTTKY-40V-300MA(SOD-323); SOD-323
Q1: BSS123; SOT23
Q2: STD36P4LLF6; DPAK-3
R4, R12: 10.0K; R-0603; TOLERANCE 5%; MPN RC0603JR-0710KL
R5: 680K; R-0603; TOLERANCE 5%; MPN RC0603JR-07680KL
R6: 0.0R; R-0603; MPN RC0603JR-070RL
R7: 0.001R; R2512
R8: 1k; R-0603; TOLERANCE 1%; MPN RC0603JR-071KL
R10: 1k; R-0603; TOLERANCE 5%; MPN RC0603JR-071KL
U2: INA199A2DCKT; SOT65P210X110-6N
X2: AK500/3

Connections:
+LOAD: C12.1, R7.2, R8.2, U2.5 (IN-), X2.1
AGND: C10.2 (-), C12.2, D2.C, Q1.2 (S), R5.1, X2.2; also elsewhere on the board
CURRENT_SENSE: C13.1, R10.1; also elsewhere on the board
EN_PIN: D3.- (C), R12.2; also elsewhere on the board
GND: C11.2, C13.2, U2.1 (REF), U2.2 (GND); also elsewhere on the board
unnamed: Q1.3 (D), R4.2, R6.2
unnamed: D2.A, R8.1
unnamed: R10.2, U2.6 (OUT)
unnamed: Q2.1 (G), R6.1
unnamed: C10.1 (+), D3.+ (A), Q1.1 (G), R5.2, R12.1
S: Q2.4 (D), R7.1, U2.4 (IN+)
VDDA: C11.1, U2.3 (V+); also elsewhere on the board
V_LOAD: Q2.3 (S), R4.1, X2.3

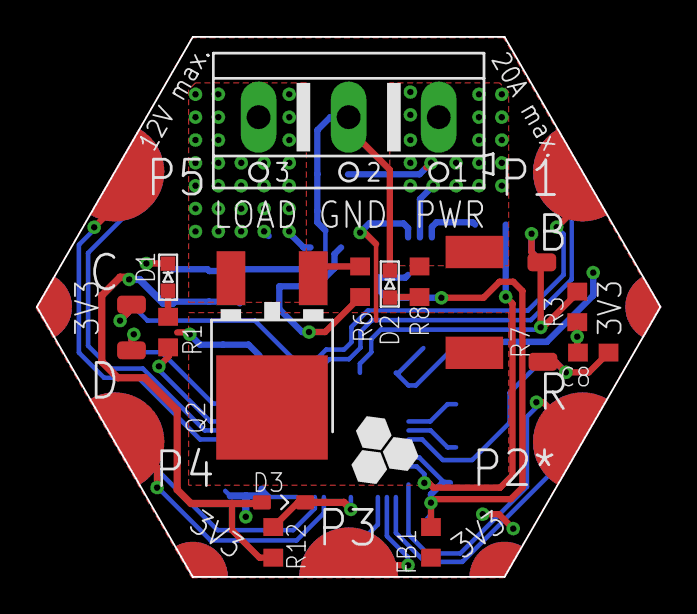
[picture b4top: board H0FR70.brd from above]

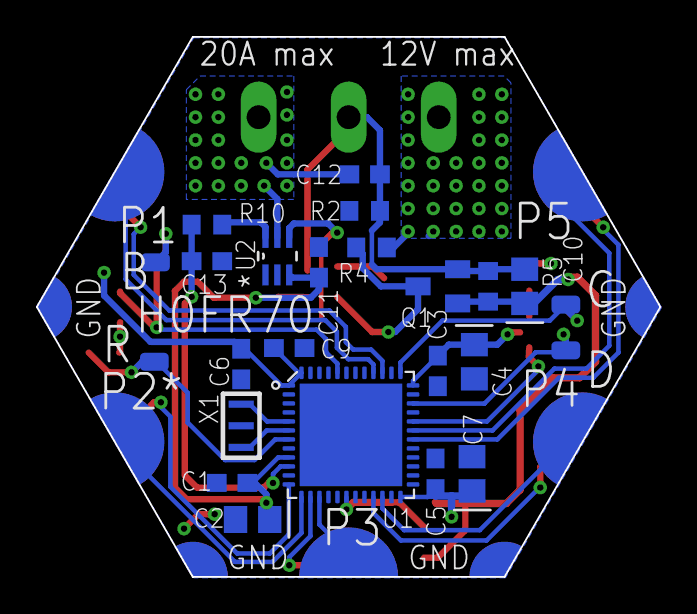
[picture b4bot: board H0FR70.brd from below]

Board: 2 copper layers, 34.6 x 30.0 mm, 38 parts (20 on the bottom side), 32 nets.

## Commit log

2020-04-06 final_unchecked power traces NOT soldered info. NOT written
2020-04-09 current sense pin connnected to PA0 (ADC_IN0) Orange indicator led in parallel with load remove power pads at top adding lables & notes
2020-04-10 fix a bug in schematics
2020-04-10 no message
2020-04-19 changing power connector to PTR500 (AK500/3) adding voltage diveder at the gate of power transistor (4.7/14.7)
2020-04-21 adding: zenar at gate + 0R res
2020-04-27 OUTPUT files were added
2020-05-19 Zener was deleted prooerties was changed to 12V 20A
2020-05-23 PDF fixed R8 changed (2k2 -> 1k) BOM modified
2022-08-15 - Changing the MC with STM32G0 - Editing the frontend design so it can work at high pwm frequencies
2022-09-11 Fix BOM file
2023-02-15 -Correcting some documentaion issues
2023-11-04 -Update the electronic & layout designs to improve the performance (the BOM have been changed too) .
2023-11-04 -Correcting some documentation issues
2023-11-05 -Add additional 10u capacitor to gate driver IC supply
2023-11-05 -Fix BOM
2024-05-26 Design modification
2024-05-28 Schematic modification
2024-06-01 -Edit the description
2024-06-18 The new Layout design for the new Electronic design has been done. Reveiwed version.
2024-07-15 -Activate the thermal option for the polygon
2025-05-31 adding the pick n place files

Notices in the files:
parts and their libraries:
COPYRIGHT: Copyright (C) 2022 Ultra Librarian. All rights reserved.
COPYRIGHT: Copyright (C) 2021 Ultra Librarian. All rights reserved.
